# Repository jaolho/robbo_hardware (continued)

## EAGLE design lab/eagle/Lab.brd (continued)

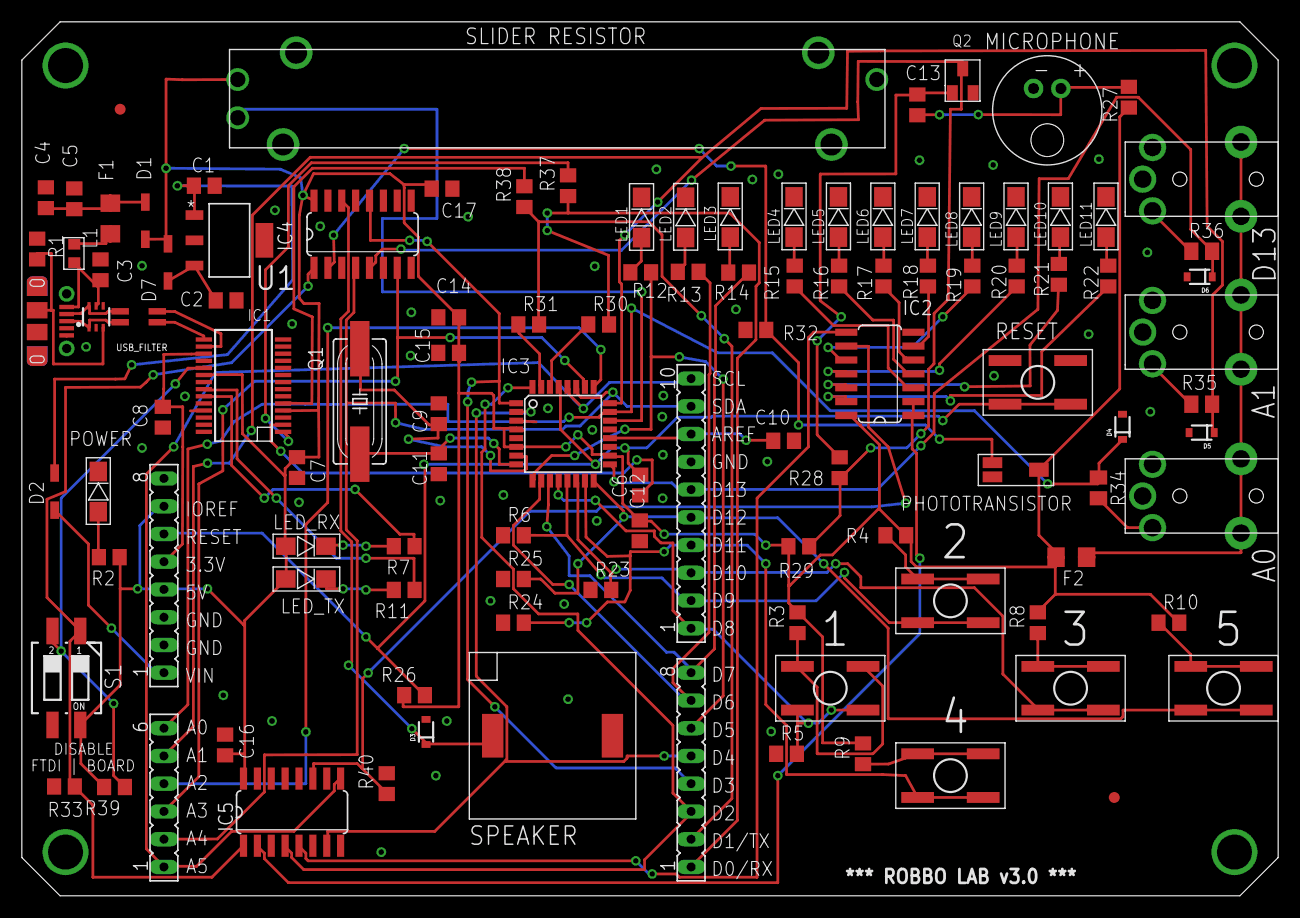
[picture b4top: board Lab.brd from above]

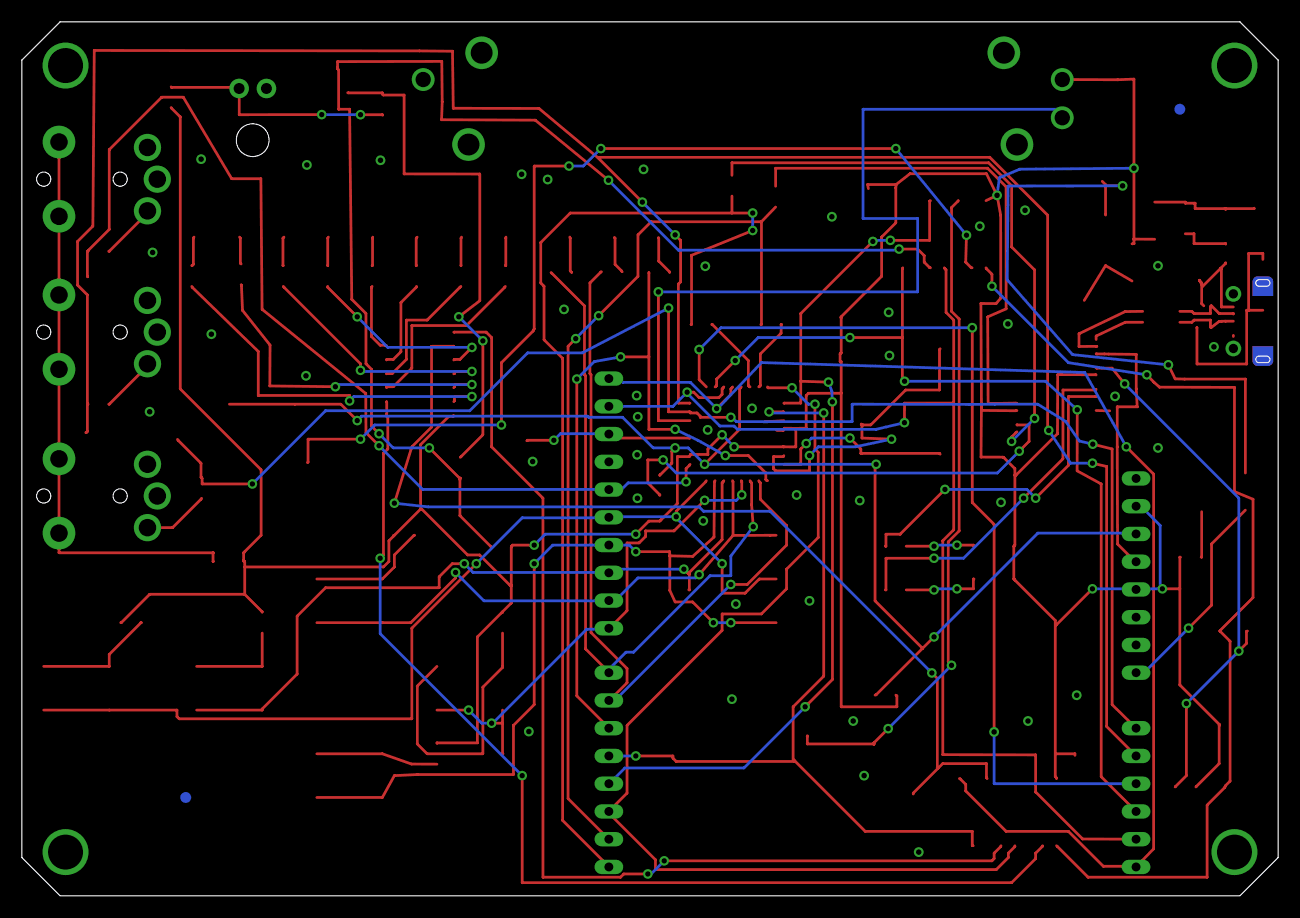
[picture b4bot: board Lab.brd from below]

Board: 2 copper layers, 115.0 x 80.0 mm, 114 parts (2 on the bottom side), 87 nets.

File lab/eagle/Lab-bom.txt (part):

Partlist exported from D:/git/sduino/lab/eagle/Lab.sch at 10/05/2016 14:38:11

Part            Value               Device             Package                        Description                             MF                          MPN                 OC_FARNELL OC_NEWARK PACKAGE   PROD_ID   SUPPLIER          VALUE
A0_CONN         FC68125             FC68125            FC68125                                                                CLIFF ELECTRONIC COMPONENTS FC68125             2309468                                                         
A1_CONN         FC68125             FC68125            FC68125                                                                CLIFF ELECTRONIC COMPONENTS FC68125             2309468                                                         
BUTTON1         KSC921J             KSC921J            TACT_SWITCH_4_PIN              Tactile Switch                          C & K COMPONENTS            KSC921J LFS         2435155                                                         
BUTTON2         KSC921J             KSC921J            TACT_SWITCH_4_PIN              Tactile Switch                          C & K COMPONENTS            KSC921J LFS         2435155                                                         
BUTTON3         KSC921J             KSC921J            TACT_SWITCH_4_PIN              Tactile Switch                          C & K COMPONENTS            KSC921J LFS         2435155                                                         
BUTTON4         KSC921J             KSC921J            TACT_SWITCH_4_PIN              Tactile Switch                          C & K COMPONENTS            KSC921J LFS         2435155                                                         
BUTTON5         KSC921J             KSC921J            TACT_SWITCH_4_PIN              Tactile Switch                          C & K COMPONENTS            KSC921J LFS         2435155                                                         
C1              330nF               C-EUC0805          C0805                          CAPACITOR, European symbol              AVX                         08053C334KAT2A      1833878                                                         
C2              100nF               C-EUC0805          C0805                          CAPACITOR, European symbol              AVX                         08055C104KAT2A      499687                                                          
C3              10nF                C-EUC0805          C0805                          CAPACITOR, European symbol              MULTICOMP                   MC0805B103K500CT    1759246                                                         
C4              4.7uF               C-EUC0805          C0805                          CAPACITOR, European symbol              WALSIN                      0805X475K250CT      2497057                                                         
C5              100nF               C-EUC0805          C0805                          CAPACITOR, European symbol              AVX                         08055C104KAT2A      499687                                                          
C6              100nF               C-EUC0805          C0805                          CAPACITOR, European symbol              AVX                         08055C104KAT2A      499687                                                          
C7              100nF               C-EUC0805          C0805                          CAPACITOR, European symbol              AVX                         08055C104KAT2A      499687                                                          
C8              100nF               C-EUC0805          C0805                          CAPACITOR, European symbol              AVX                         08055C104KAT2A      499687                                                          
C9              22pF                C-EUC0805          C0805                          CAPACITOR, European symbol              YAGEO (PHYCOMP)             CC0805JRNPO9BN220   1362555                                                         
C10             100nF               C-EUC0805          C0805                          CAPACITOR, European symbol              AVX                         08055C104KAT2A      499687                                                          
C11             22pF                C-EUC0805          C0805                          CAPACITOR, European symbol              YAGEO (PHYCOMP)             CC0805JRNPO9BN220   1362555                                                         
C12             100nF               C-EUC0805          C0805                          CAPACITOR, European symbol              AVX                         08055C104KAT2A      499687                                                          
C13             470nF               C-EUC0805          C0805                          CAPACITOR, European symbol              MULTICOMP                   MC0805F474Z250CT    1759175                                                         
C14             4.7uF               C-EUC0805          C0805                          CAPACITOR, European symbol              WALSIN                      0805X475K250CT      2497057                                                         
C15             100nF               C-EUC0805          C0805                          CAPACITOR, European symbol              AVX                         08055C104KAT2A      499687                                                          
C16             100nF               C-EUC0805          C0805                          CAPACITOR, European symbol              AVX                         08055C104KAT2A      499687                                                          
C17             100nF               C-EUC0805          C0805                          CAPACITOR, European symbol              AVX                         08055C104KAT2A      499687                                                          
D0_CONN         FC68125             FC68125            FC68125                                                                CLIFF ELECTRONIC COMPONENTS FC68125             2309468                                                         
D1              MBR0520             MBR0520            SOD123                         Schottky diode                          FAIRCHILD SEMICONDUCTOR     MBR0520L            1467521                                                         
D2              MBR0520             MBR0520            SOD123                         Schottky diode                          FAIRCHILD SEMICONDUCTOR     MBR0520L            1467521                                                         
D3              5.1V                DIODE-ZENER5.6V    SOD-323                        Zener Diode                             ON SEMICONDUCTOR            MM3Z5V1T1G          1431203                        DIO-12442                   5.6V 
D4              5.1V                DIODE-ZENER5.6V    SOD-323                        Zener Diode                             ON SEMICONDUCTOR            MM3Z5V1T1G          1431203                        DIO-12442                   5.6V 
D5              5.1V                DIODE-ZENER5.6V    SOD-323                        Zener Diode                             ON SEMICONDUCTOR            MM3Z5V1T1G          1431203                        DIO-12442                   5.6V 
D6              5.1V                DIODE-ZENER5.6V    SOD-323                        Zener Diode                             ON SEMICONDUCTOR            MM3Z5V1T1G          1431203                        DIO-12442                   5.6V 
D7              MBR0520             MBR0520            SOD123                         Schottky diode                          FAIRCHILD SEMICONDUCTOR     MBR0520L            1467521                                                         
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
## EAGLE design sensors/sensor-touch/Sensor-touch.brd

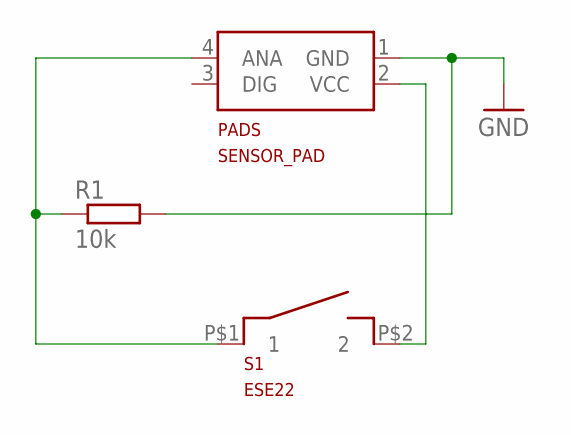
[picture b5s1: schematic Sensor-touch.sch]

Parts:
PADS: SENSOR_PAD
R1: 10k; R0805; MPN RC0805FR-0710KL
S1: ESE22; MPN ESE-22MH24

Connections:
GND: PADS.1 (GND), R1.2
unnamed: PADS.4 (ANA), R1.1, S1.P$1 (1)
unnamed: PADS.2 (VCC), S1.P$2 (2)

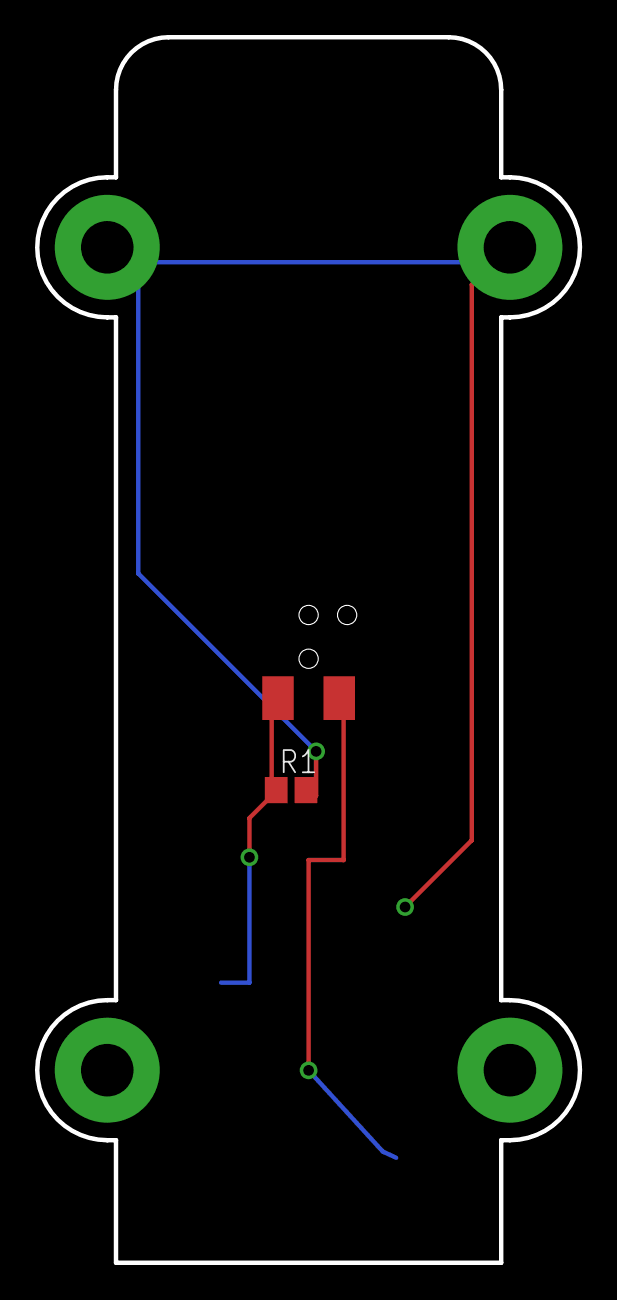
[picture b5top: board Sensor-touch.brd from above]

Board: 2 copper layers, 31.0 x 70.0 mm, 3 parts (0 on the bottom side), 3 nets.

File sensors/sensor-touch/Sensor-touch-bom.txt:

Partlist exported from D:/git/sduino/sensors/sensor-touch/Sensor-touch.sch at 22/12/2015 13:48:00

Part Value      Device     Package    Description               MF                              MPN             OC_FARNELL
PADS SENSOR_PAD SENSOR_PAD SENSOR_PAD                                                                           unknown   
R1   10k        R-EU_R0805 R0805      RESISTOR, European symbol YAGEO (PHYCOMP)                 RC0805FR-0710KL 9237755   
S1   ESE22      ESE22      ESE22                                PANASONIC ELECTRONIC COMPONENTS ESE-22MH24      2459516

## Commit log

2016-09-02 Repo created.
